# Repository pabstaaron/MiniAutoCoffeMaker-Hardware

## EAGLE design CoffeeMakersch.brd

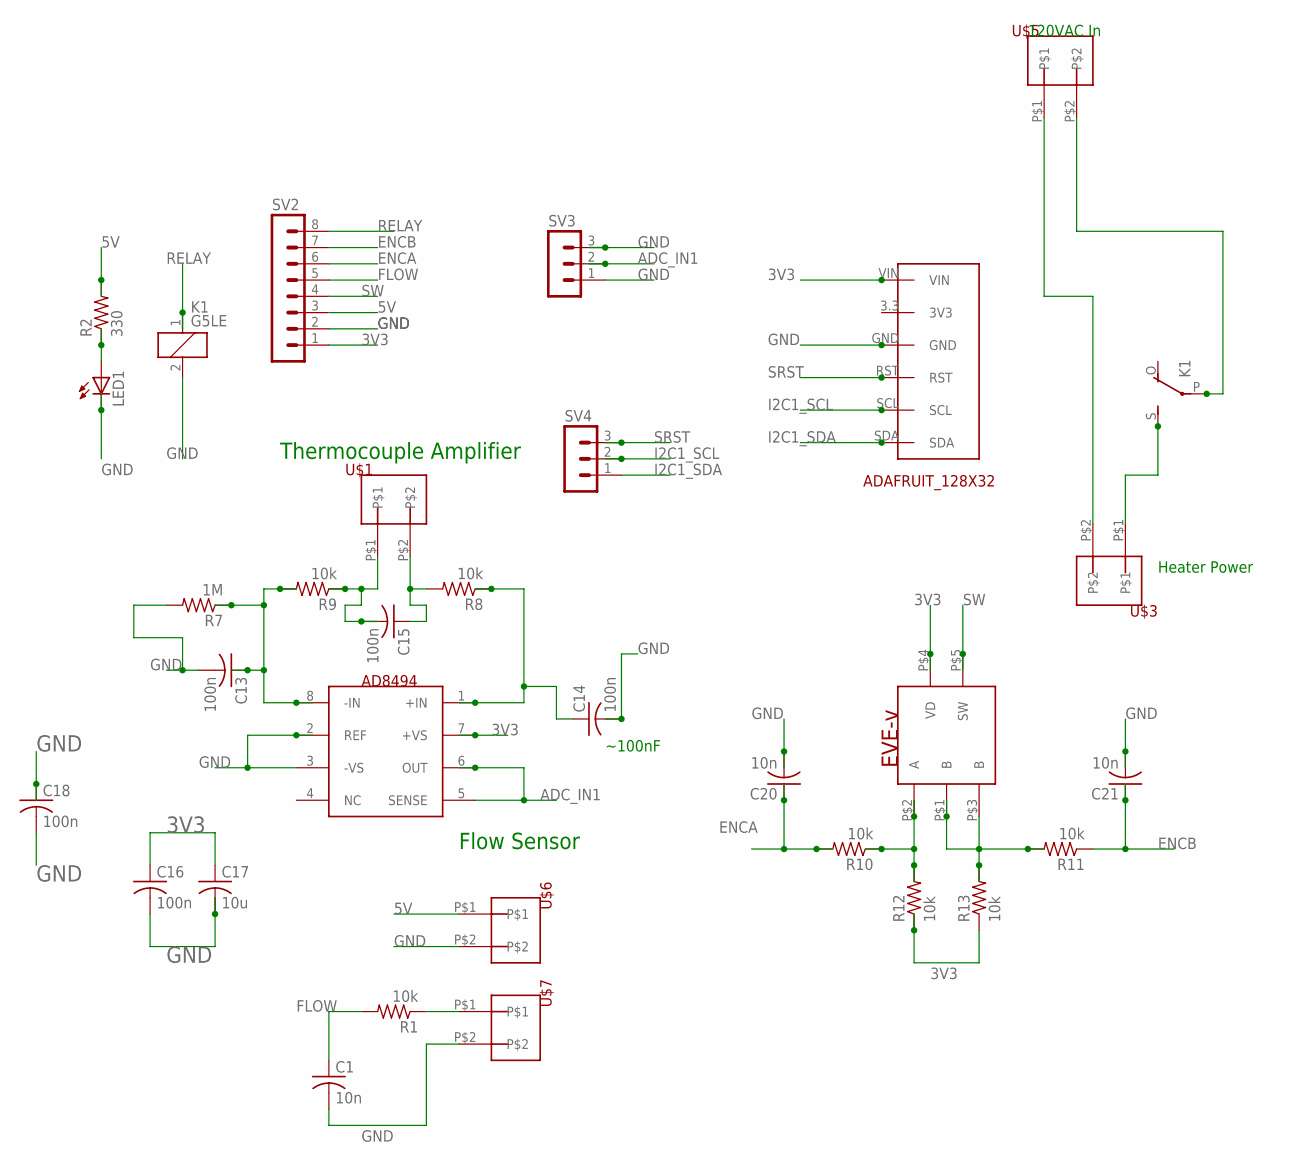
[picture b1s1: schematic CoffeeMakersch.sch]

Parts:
C1, C20, C21: 10n; C0805
C13, C14, C15, C16, C18: 100n; C0805
C17: 10u; C0805
K1: G5LE
LED1: LEDCHIPLED_1206; CHIPLED_1206
R1, R8, R9, R10, R11, R12, R13: 10k; R0805
R2: 330; R0805
R7: 1M; R0805
SV2: MA08-1
SV3, SV4: MA03-1
U$1, U$3, U$5, U$6, U$7: 5TERM
U$2: AD8494; TSSOP8
U$4: EVE-V
U$11: ADAFRUIT_128X32; ADAFRUIT128X32

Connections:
3V3: C16.1, C17.1, R12.1, R13.1, SV2.1, U$2.7 (+VS), U$4.P$4 (VD), U$11.VIN
5V: R2.2, SV2.3, U$6.P$1
ADC_IN1: SV3.2, U$2.5 (SENSE), U$2.6 (OUT)
ENCA: C20.1, R10.2, SV2.6
ENCB: C21.1, R11.1, SV2.7
FLOW: C1.1, R1.2, SV2.5
GND: C1.2, C13.2, C14.2, C16.2, C17.2, C18.1, C18.2, C20.2, C21.2, K1.2, LED1.C, R7.2, SV2.2, SV3.1, SV3.3, U$2.2 (REF), U$2.3 (-VS), U$6.P$2, U$7.P$2, U$11.GND
I2C1_SCL: SV4.2, U$11.SCL
I2C1_SDA: SV4.1, U$11.SDA
unnamed: R1.1, U$7.P$1
unnamed: K1.P, U$5.P$2
unnamed: U$3.P$2, U$5.P$1
unnamed: K1.S, U$3.P$1
unnamed: LED1.A, R2.1
unnamed: C13.1, R7.1, R9.2, U$2.8 (-IN)
unnamed: C14.1, R8.1, U$2.1 (+IN)
unnamed: C15.1, R8.2, U$1.P$2
unnamed: C15.2, R9.1, U$1.P$1
unnamed: R10.1, R12.2, U$4.P$2 (A)
unnamed: R11.2, R13.2, U$4.P$1 (B), U$4.P$3 (B)
RELAY: K1.1, SV2.8
SRST: SV4.3, U$11.RST
SW: SV2.4, U$4.P$5 (SW)

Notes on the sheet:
120VAC In
Heater Power
Thermocouple Amplifier
Flow Sensor
~100nF

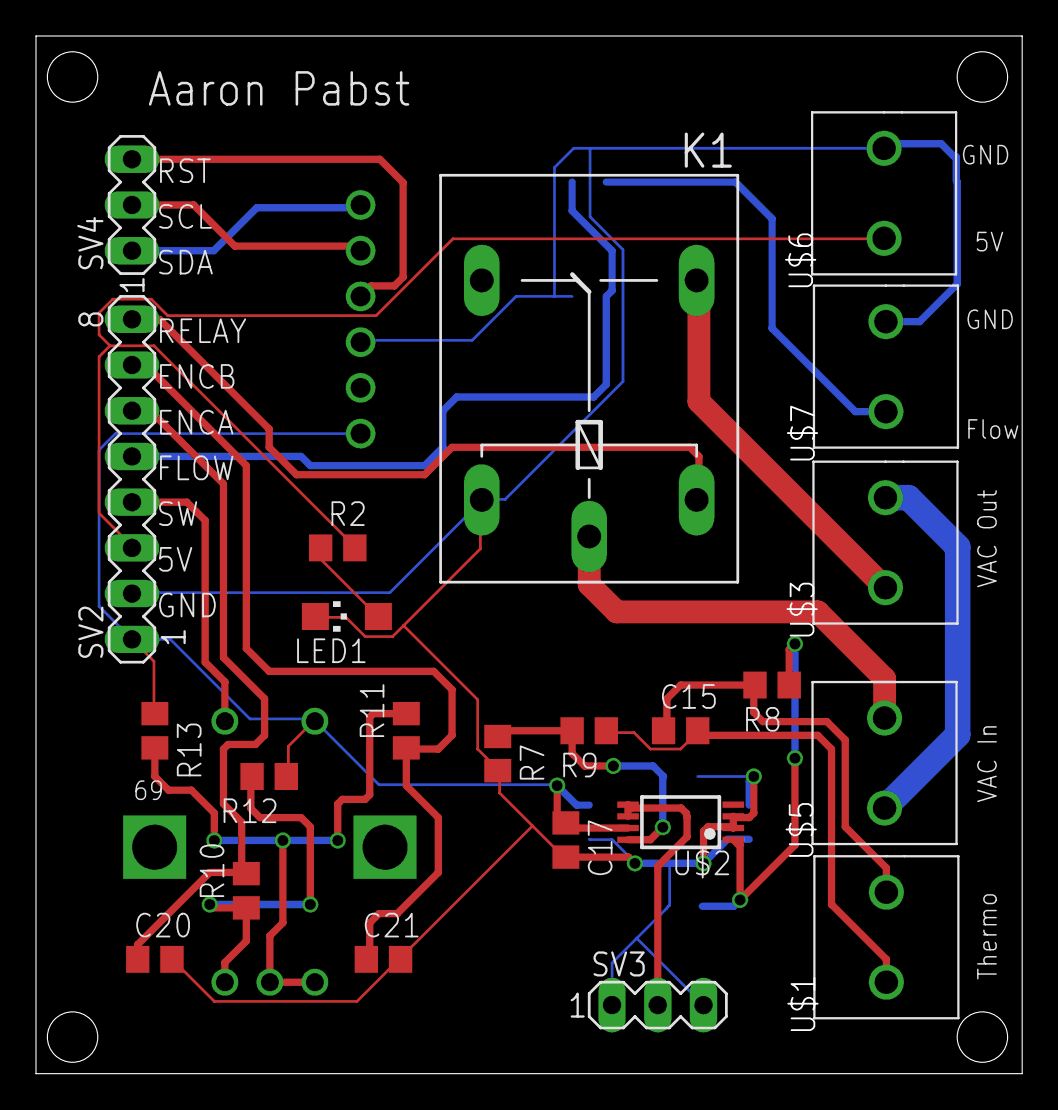
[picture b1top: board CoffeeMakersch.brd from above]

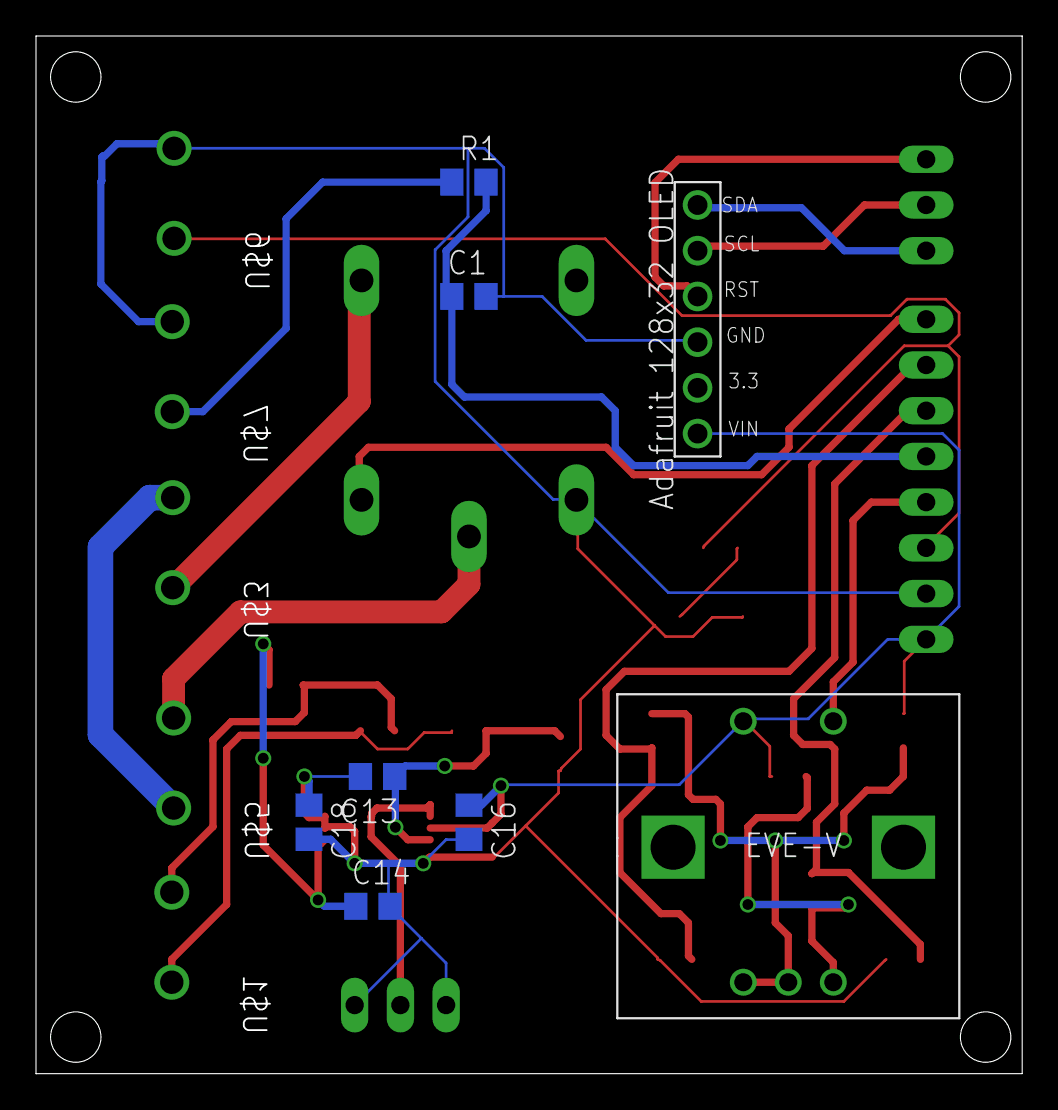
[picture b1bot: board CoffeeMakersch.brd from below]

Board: 2 copper layers, 54.8 x 57.6 mm, 31 parts (8 on the bottom side), 23 nets.

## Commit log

2018-04-09 Finished schematic
2018-04-20 Finished schematic and board files
